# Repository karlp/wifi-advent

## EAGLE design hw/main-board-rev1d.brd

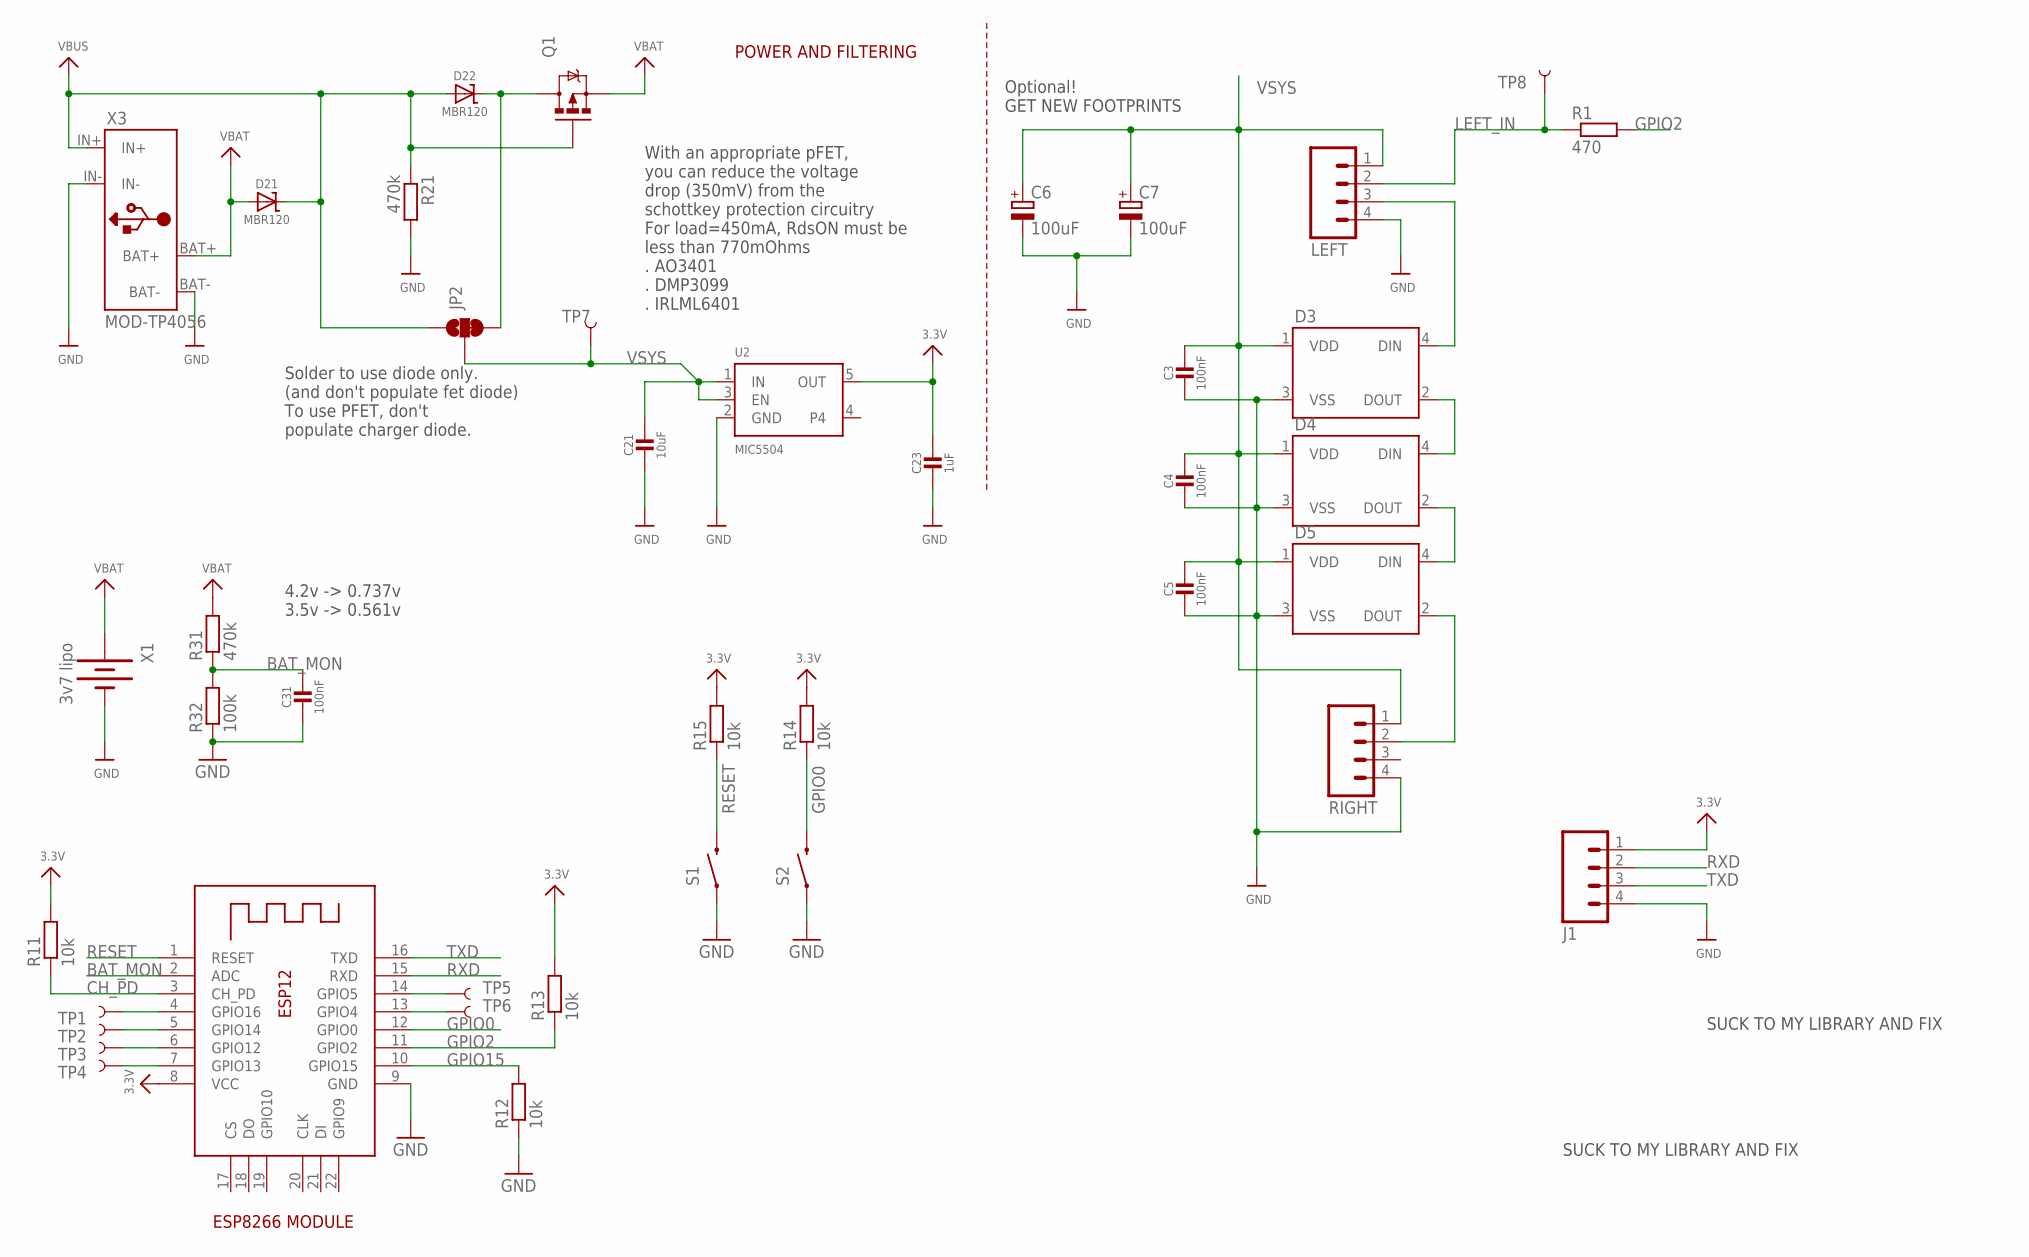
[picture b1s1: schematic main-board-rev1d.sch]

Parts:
C3, C4, C5, C31: 100nF; 0805-NO
C6, C7: 100uF; PANASONIC_B
C21: 10uF; 0805-NO
C23: 1uF; 0805-NO
D3, D4, D5: WS2812B
D21, D22: MBR120; SOD-123
J1: M041X04_NO_SILK; 1X04_NO_SILK
JP2: JUMPER-PAD-3-2OF3_NC_BY_TRACE_LARGE; PAD-JUMPER-3-2OF3_NC_BY_TRACE_YES_SILK_LARGE
LEFT: M041X04_NO_SILK; 1X04_NO_SILK
Q1: MOSFET-PCHANNEL; SOT23-3
R1: 470; R0603
R11, R12, R13, R14, R15: 10k; R0603
R21, R31: 470k; R0603
R32: 100k; R0603
RIGHT: M041X04_NO_SILK; 1X04_NO_SILK
S1, S2: SWITCH-MOMENTARY-2PTH; TACTILE-PTH
TP1, TP2, TP3, TP4, TP5, TP6, TP7, TP8: TEST-POINTTP_06_TH; TP_06TH
U2: MIC5504; SOT23-5
X1: 3v7 lipo; BATT-18650-BLOSSOM-1
X2: ESP-12; ESP-12E
X3: MOD-TP4056; MOD-LIPO_CHARGER

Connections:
3.3V: C23.1, J1.1, R11.2, R13.2, R14.2, R15.2, U2.5 (OUT), X2.8 (VCC)
BAT_MON: C31.1, R31.1, R32.2, X2.2 (ADC)
CH_PD: R11.1, X2.3 (CH_PD)
D3_IN: D3.4 (DIN), LEFT.3
D4_IN: D3.2 (DOUT), D4.4 (DIN)
D5_IN: D4.2 (DOUT), D5.4 (DIN)
GND: C3.2, C4.2, C5.2, C6.-, C7.-, C21.2, C23.2, C31.2, D3.3 (VSS), D4.3 (VSS), D5.3 (VSS), J1.4, LEFT.4, R12.1, R21.2, R32.1, RIGHT.4, S1.1, S2.1, U2.2 (GND), X1.-, X2.9 (GND), X3.BAT-, X3.IN-
GPIO0: R14.1, S2.3 (2), X2.12 (GPIO0)
GPIO2: R1.2, R13.1, X2.11 (GPIO2)
GPIO15: R12.2, X2.10 (GPIO15)
LEFT_IN: LEFT.2, R1.1, TP8.P$1
unnamed: TP1.P$1, X2.4 (GPIO16)
unnamed: TP2.P$1, X2.5 (GPIO14)
unnamed: D22.C, JP2.3, Q1.3 (D)
unnamed: TP3.P$1, X2.6 (GPIO12)
unnamed: TP4.P$1, X2.7 (GPIO13)
unnamed: TP5.P$1, X2.14 (GPIO5)
unnamed: TP6.P$1, X2.13 (GPIO4)
RESET: R15.1, S1.3 (2), X2.1 (RESET)
RIGHT_IN: D5.2 (DOUT), RIGHT.2
RXD: J1.2, X2.15 (RXD)
TXD: J1.3, X2.16 (TXD)
VBAT: D21.A, Q1.2 (S), R31.2, X1.+, X3.BAT+
VBUS: D21.C, D22.A, JP2.1, Q1.1 (G), R21.1, X3.IN+
VSYS: C3.1, C4.1, C5.1, C6.+, C7.+, C21.1, D3.1 (VDD), D4.1 (VDD), D5.1 (VDD), JP2.2, LEFT.1, RIGHT.1, TP7.P$1, U2.1 (IN), U2.3 (EN)

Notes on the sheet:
POWER AND FILTERING
ESP8266 MODULE
Optional! GET NEW FOOTPRINTS
4.2v -> 0.737v 3.5v -> 0.561v
With an appropriate pFET, you can reduce the voltage drop (350mV) from the schottkey protection circuitry For load=450mA, RdsON must be less than 770mOhms . AO3401 . DMP3099 . IRLML6401
Solder to use diode only. (and don't populate fet diode) To use PFET, don't populate charger diode.
SUCK TO MY LIBRARY AND FIX

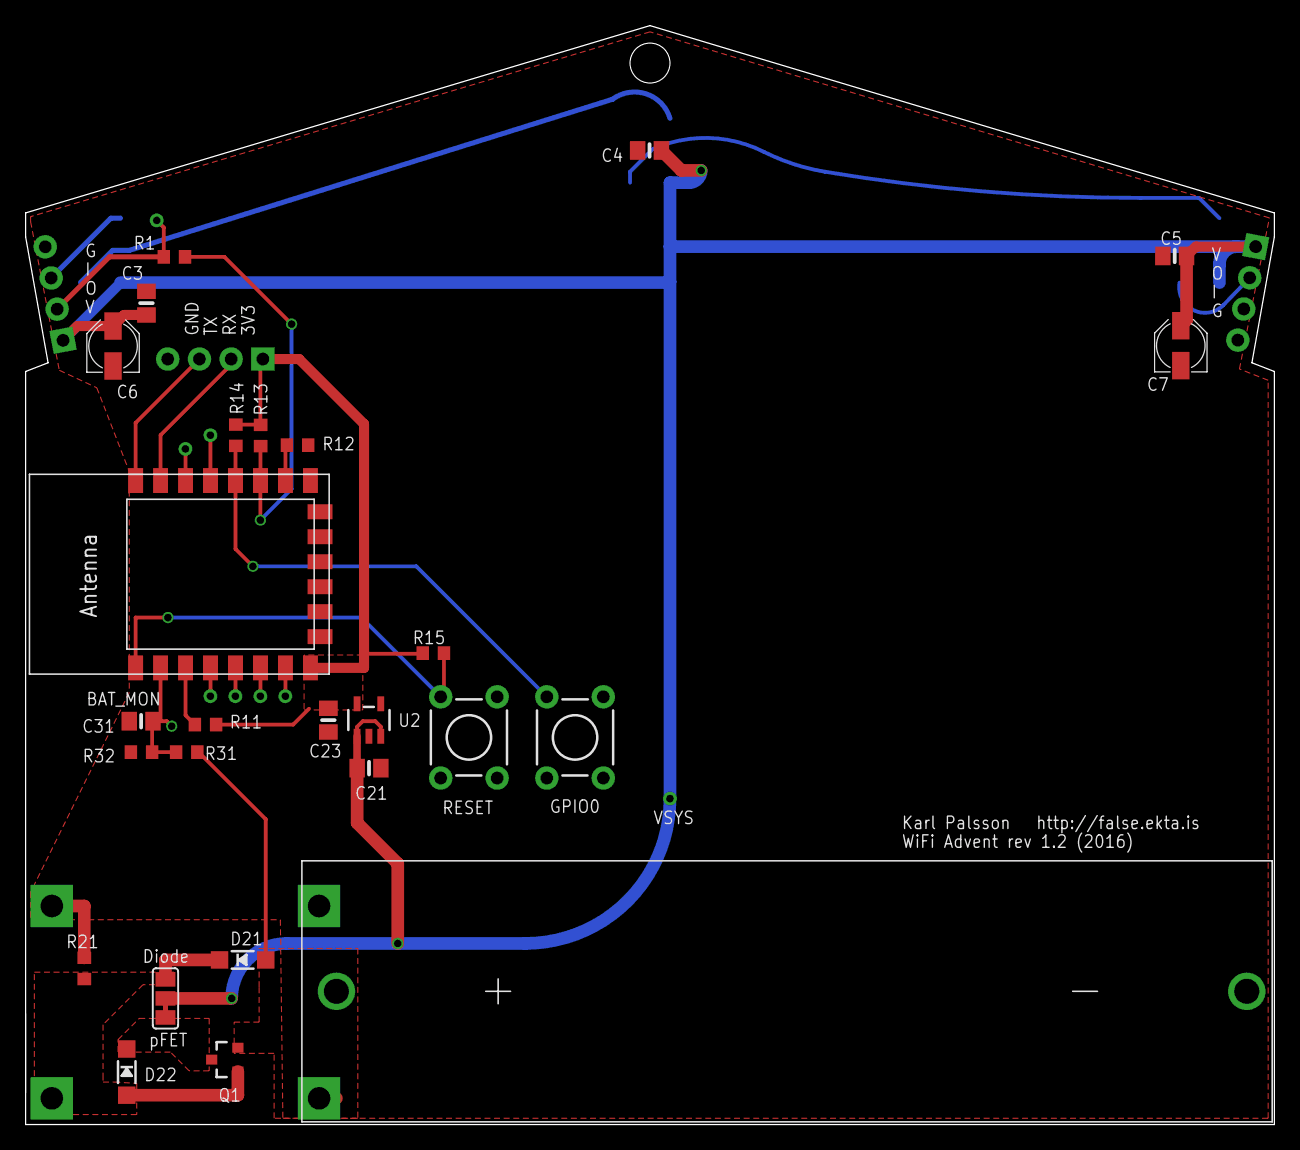
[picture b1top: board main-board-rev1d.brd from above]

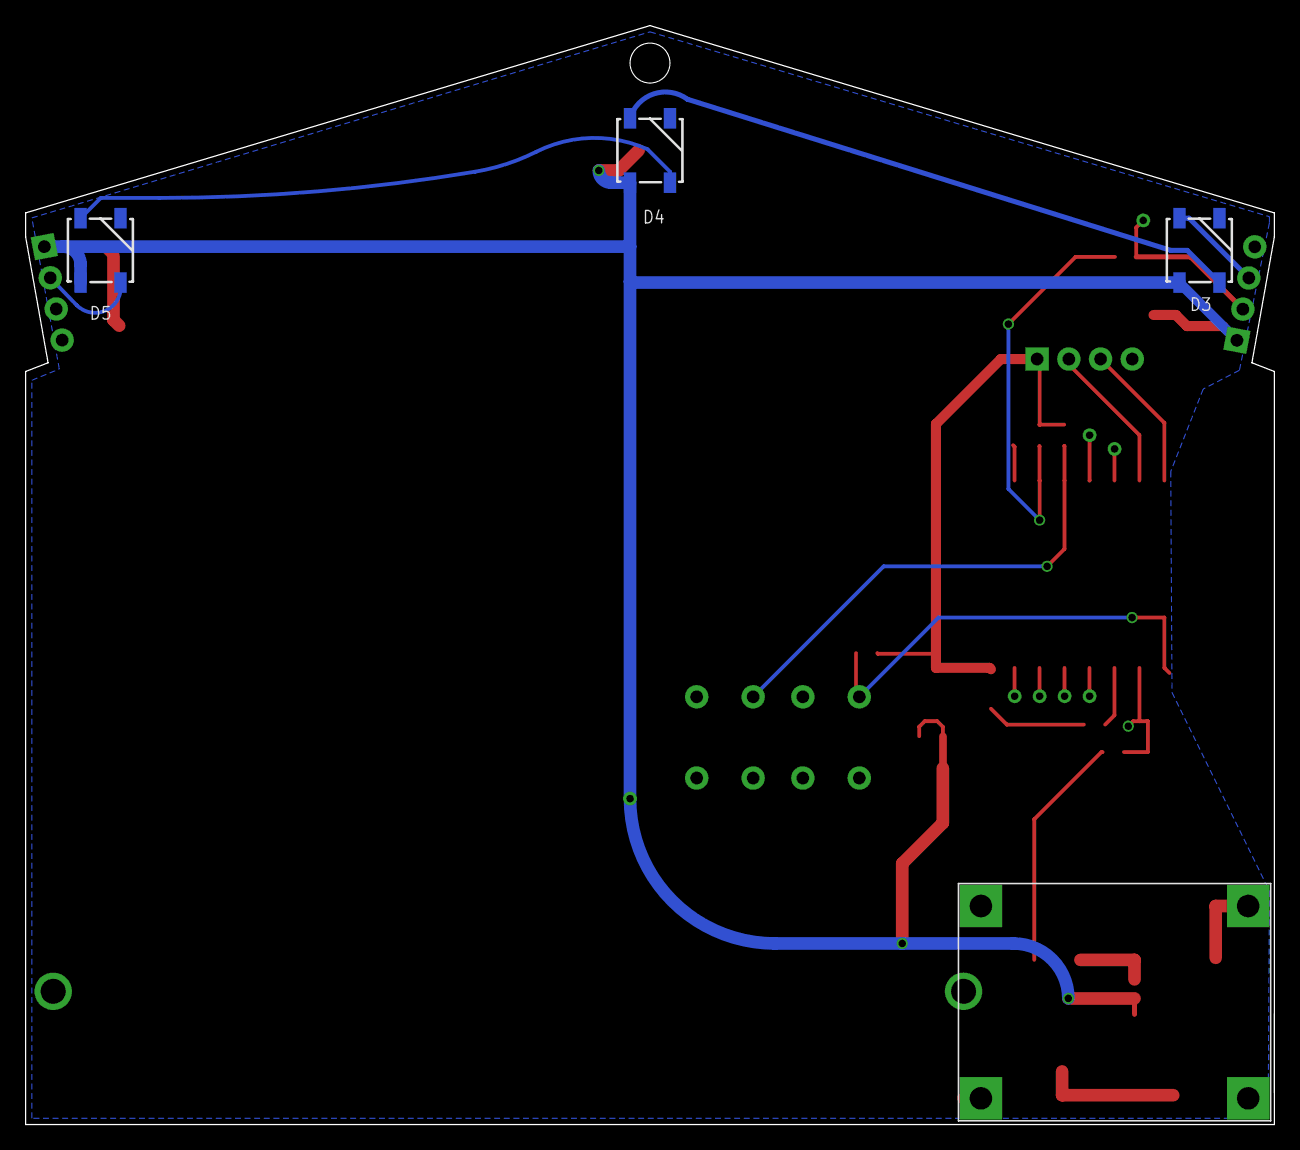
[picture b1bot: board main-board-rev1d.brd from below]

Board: 2 copper layers, 100.0 x 88.0 mm, 41 parts (5 on the bottom side), 25 nets.

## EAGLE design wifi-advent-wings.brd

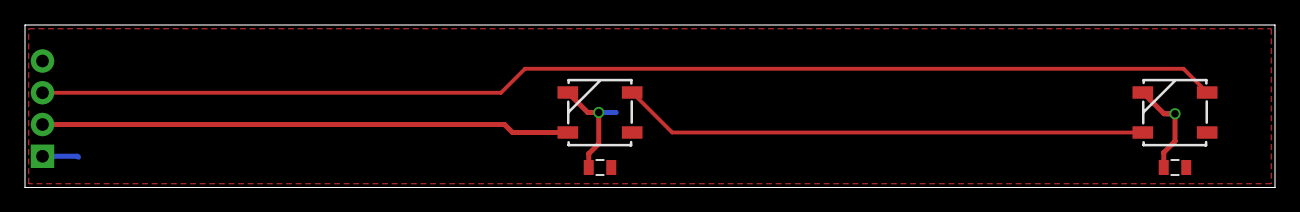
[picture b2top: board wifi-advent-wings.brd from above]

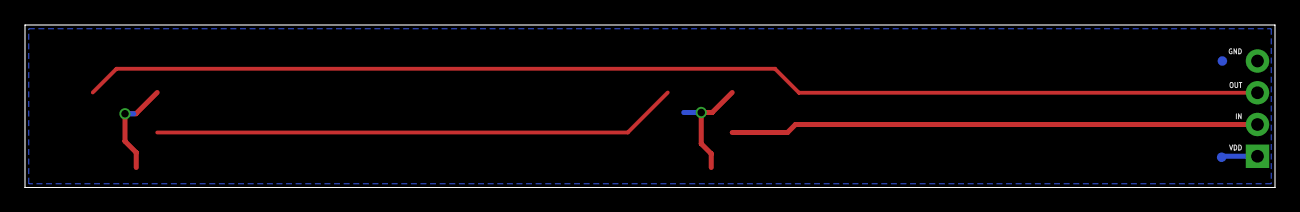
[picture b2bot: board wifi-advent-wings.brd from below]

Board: 2 copper layers, 100.0 x 13.0 mm, 7 parts (2 on the bottom side), 5 nets.

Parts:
C1, C2: 0805
D1, D2: WS2812B
J1: 1X04_NO_SILK
TP1: VDD; PAD.03X.03
TP2: GND; PAD.03X.03

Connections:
GND: C1.2, C2.2, D1.3, D2.3, J1.4, TP2.P$1
IN: D1.4, J1.2
unnamed: D1.2, D2.4
OUT: D2.2, J1.3
VDD: C1.1, C2.1, D1.1, D2.1, J1.1, TP1.P$1

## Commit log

2016-10-18 wings: intial pcb
    Should have had this from the beginning, but ok.
2016-10-18 central board: "initial" schematic/board
    Board is unrouted, but leds are placed and fixed.
    Schematic is _provisionally_ complete.
2016-10-18 notes on which pins can control leds with existing libraries
2016-10-18 new parts library
    Some imported from old designs, some new. Some redrawn
2016-10-18 basic test that the leds all work.
2016-10-18 gerbmerge files for wings layout
2016-10-19 library: add blossom 18650 single battery holder
2016-10-20 updates listed below
    * used blossom battery case
    * switched to 100uF big fat smds for "bulk" ws2812 support
    * fixed values for vbat monitoring divider and added cap to hold it
2016-10-25 smash and fix all silk
    Add notes on connectors and test points
2016-10-25 Routed all basic signals
    Going to hold here and use all that space to put in the pfet+diode
    method as well as just optional footprints.
    only get one build
2016-10-25 make all caps consistent footprints
    split VSYS into two forks to distribute power better. even at 1mm wide,
    trace resistance is estimted at 300mOhm. (but that's for the whole
    lenght, not longest fork)
2016-10-25 added optional pfet+diode power path instead of diode
    fully routed, corrected error with (non)rotated wings.
2016-10-25 add polygon for vbat
2016-10-25 gitignore backups and stuff
2016-10-25 library: tp4056 module fix silk layers
    Wildly inconsistent. hope the dimension is right!
2016-10-25 remove duplicate wires on optional caps
    stupid schematic capture
2016-10-25 Align buttons
2016-10-25 remove superfluous cutout for usb
2016-10-25 Add revision and author text
2016-10-26 Pull ground back from antenna
2016-10-28 push hw files down a level
2016-10-28 add nodemcu as submodule
2016-11-13 fw: Basic arduino ota+leds
    massive missing holes already. but progress is progress
2016-11-13 nodemcu: include demo of enduser setup
2016-11-13 Add esp8266 arduino as submodule
    we're going to need to fix upstream :(
2016-11-15 neat fet solution
2016-11-18 fw: platformio version1
    A little easier to build and work with than the arduino IDE, but
    virutally identical to the "ard/combo-ota1" sketch.
    Uses my own fork of arduino with the OTA callbacks added (submitted
    upstream already)
2016-11-18 fw: explicitly include NeoPixelBus
2016-11-18 pio1: whitespace autoformat
    carryover from bringing this pile over from arduino ide
2016-11-18 add basicccc end user setup
    Needs a bit more poking to behave well with restart/reconfig but pretty
    close.
2016-11-22 pio: update library deps
2016-11-22 pio: set led count for dev board
    We can go back to 7 when we have real hardware
2016-11-22 pio: fix leds in OTA update + basic mqtt
    Should be split in two, bad karl!
    leds were missing strip.Show()! The animation handler was fixing that
    internally, but is required if you're fiddling yourself. Other commands
    are only updating the internal states.
    MQTT publishing seems to work, but it crashes in the onMessageHandler
    for some reason.
2016-11-26 emergency rev1d draft
    stupid polygon rank screwup. I _know_ I handled this, but somewhere it
    got lost and reset, and the final gerbers had all the polys joined again
    :(
    seeing as we're redoing, put notches for the wings, allows both flush
    with wire and through hole mounts.
    Also, move the esp8266 module to the board edge to give the antenna a
2016-11-26 change default grid to metric
2016-11-26 tp4056 module: make fit modules received better
    Original sourced from the internet _worked_ but the pins were a bit
    skewed.
    Changes: expand drills, reduce pads.
2016-11-26 battery: blossom: use slightly more sane drills
    Based on the received hardware. the 2.4mm drill specified in the
    datasheet is way pessimistic. The datasheet was spot on for the pins on
    the device, no idea why they were so pessimistic for the pcb pattern.
2016-11-26 hw rev 1.2
    Moved module to side for "proper" rf.
    Fixed rotated wing connectors
    Fixed overlapping polygon pours
    Relaid out almost all of the lower section
    Added more test points, and all spare ios on ESPmodule
2016-11-26 lib: add test points
    Originall from sparkfun, but with a through hole one modified to 0.6mm
    drill which matches basic vias, that I can stuff cat5 strands into in a
    pinch.
2016-11-28 pio: add missing arduinojson dep
2016-12-01 See changelist
    Ticker for led handling so that mqtt messages don't crash.
    Private ticker class (pull request sent) to enable easy "still active"
    checking
    File handling and basic default files for spiffs
    Needs: uploader support for spiffs image.
2016-12-05 support spiffs upload as well
2016-12-05 Use hash of chip id as default password
    And properly use it as the host/ssid too.
2016-12-05 blink leds via ticker for mqtt
    Same as before, avoids panic when the disconnect hits
2016-12-05 Drop MQTT: not used, some problems
    Will come back, but wills are failing, and initial target won't have
    wifi anyway, nor is the mqtt infrastructure ready.
2016-12-06 Hack async wifi manager
    Exception 28 with mdns sometimes :(
2016-12-07 pio: use fast serial uploads plz
2016-12-07 pio: final led count for real hw now
2016-12-07 improving debug
2016-12-07 disable dns captive portal (exception 28)
    something here is causing exception code 28 with my _async changes. I
    don't stricly _need_ the captive portal portions, (going to 192.168.4.1
    is ok when it's in AP mode) so just turn it off.
2016-12-08 Reenble mdns now that it works again
2016-12-08 monster: restore mqtt and start anims
2016-12-08 comments and dbeug
2016-12-08 properly block mqtt when we're updating.
    reconnection attempts were crashing it.
2016-12-09 Vile hacky bootstrap
    too many static files, nowhere near clever enough at using client side
    resources!
    my js/html foo is too weak to knock this out quickly!
2016-12-09 Basic support for setting led patterns via web.
    no ui, json config only
2016-12-09 pio: rename bootstrap fonts to avoid spiffs bug
    spiffs limits max filenames to 32. this causes failures trying to read
    the font files, which empiracally has a major impact on latency in the
    webserver. modify the bootstrap file and rename the font files, and the
    web server is _much_ more responsive!
2016-12-09 turn off gdb stuff
    seems to cause flash limit overflows on one computer?
2016-12-09 faster pixel updates please
    The centiseconds might be useful for some longer effects, but was
    basically just making things slow.
2016-12-09 slightly better colour choice via hsl
    easier to think
2016-12-09 mqtt: fix will
    Because async mqtt is _fulllllly_ async, it doesn't actually copy/store
    the will topic and use it when you call connect, it jsut fires off the
    tcp connect and tries to use the will when that actually finishes.
    However, at that time, the dynamic will String had gone out of scope,
    and so was considered invalid => no will.
    Use a global for now. Wills now work at least.
2016-12-09 fix json reply to clients
2018-01-05 hw1: notes after assembling rev1
2018-01-05 basic vids and pics of operations
2018-01-05 archive initial release build
2018-01-05 mailed out instructions
2021-11-29 hw: Initial stab of new gen single pcb
    through hole diffused leds and esp32 instead.

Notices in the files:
hw/main-board-rev1d.sch:
COPYRIGHT: 2016
parts and their libraries:
microbuilder: This work is placed in the public domain, and may be freely used for commercial and non-commercial work with the following conditions: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
SparkFun-Connectors: Licensing: Creative Commons ShareAlike 4.0 International - https://creativecommons.org/licenses/by-sa/4.0
